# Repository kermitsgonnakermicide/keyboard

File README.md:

# keyboard

a travel sized 60% keyboard with two rotary encoders for extra functionality!<br>

## Design<br>

This keyboard is pretty **bog-standard**, and can be split into two basic components; the PCB and case<br>
**PCB**:<br>
Fully through hole, with a raspberry pi pico, in4018 diodes and HMX macchiato switches(cheap + sound awesome!)<br>
Went fully THT to keep costs as low as I can, and get some real soldering in!<br>
**Case**:<BR>
Just a case covering the entire keyboard t_t
Again, owing to the purpose of the keyboard, I want to keep it small and simple, but for the shiggles I addded this cool pattern to the bottom of my case<br>
<br>

**Firmware**:<br>
Again, pretty standard KMK firmware running on the pico<br>
<br>

## Images

<br>
<br>
<BR>
<br>

### Images of the CAD

## BOM

| ITEM                        | QTY | TOTAL  | SRC                                                                                                                                                                                                                                                                                                                                                                                                                                                                                                                                                                                                                                                                                                                                                                                                                                                                                                                                                                                                                                                                                                                                                                                            | NOTE                                 |
| --------------------------- | --- | ------ | ---------------------------------------------------------------------------------------------------------------------------------------------------------------------------------------------------------------------------------------------------------------------------------------------------------------------------------------------------------------------------------------------------------------------------------------------------------------------------------------------------------------------------------------------------------------------------------------------------------------------------------------------------------------------------------------------------------------------------------------------------------------------------------------------------------------------------------------------------------------------------------------------------------------------------------------------------------------------------------------------------------------------------------------------------------------------------------------------------------------------------------------------------------------------------------------------- | ------------------------------------ |
| HMX Macchiato Linear Switch | 7   | 24.35  | [https://neomacro.in/products/keykobo-rainbow?variant=48680982413590](https://neomacro.in/products/keykobo-rainbow?variant=48680982413590)                                                                                                                                                                                                                                                                                                                                                                                                                                                                                                                                                                                                                                                                                                                                                                                                                                                                                                                                                                                                                                                     | Sold in packs of 10 and I require 62 |
| KeyKobo Rainbow Keycap      | 1   | 43.48  | [https://neomacro.in/products/keykobo-rainbow?variant=48680982413590](https://neomacro.in/products/keykobo-rainbow?variant=48680982413590)                                                                                                                                                                                                                                                                                                                                                                                                                                                                                                                                                                                                                                                                                                                                                                                                                                                                                                                                                                                                                                                     |                                      |
| Raspberry Pi Pico 2         | 1   | 4.79   | [https://www.amazon.in/Raspberry-Pico-All-Microcontroller-Board/dp/B0B69KZBD8/ref=sr_1_1?crid=2SX0N4M63ZWH0&dib=eyJ2IjoiMSJ9.AG5JhGRrljClCgda-pmbDiD1qgK6UMgZNUfO6lCjvNRDwukhXHZauoI63nwYufeCMjrTgOu-PR4EB1B7bBTxMx_hHgDObzbV_989GRUKeAKs9bf6mNNWnI8RB88uI3AtziqfbLDEnSlC9C45SWxsgeOhS_r8351-swVnHh5PpfJFPoSv4LKkKSLkdM34SVLB4KbwTGd2ggQV1Gwpf81-vTKtUTg3C4Jg-lUPle1kBh8.S8F72l44oyaOFh3p5GCZGWSFGbHGolIi6mE-abOFBGI&dib_tag=se&keywords=raspi+pico&qid=1755337610&sprefix=raspi+pic,aps,281&sr=8-1&th=1](https://www.amazon.in/Raspberry-Pico-All-Microcontroller-Board/dp/B0B69KZBD8/ref=sr_1_1?crid=2SX0N4M63ZWH0&dib=eyJ2IjoiMSJ9.AG5JhGRrljClCgda-pmbDiD1qgK6UMgZNUfO6lCjvNRDwukhXHZauoI63nwYufeCMjrTgOu-PR4EB1B7bBTxMx_hHgDObzbV_989GRUKeAKs9bf6mNNWnI8RB88uI3AtziqfbLDEnSlC9C45SWxsgeOhS_r8351-swVnHh5PpfJFPoSv4LKkKSLkdM34SVLB4KbwTGd2ggQV1Gwpf81-vTKtUTg3C4Jg-lUPle1kBh8.S8F72l44oyaOFh3p5GCZGWSFGbHGolIi6mE-abOFBGI&dib_tag=se&keywords=raspi+pico&qid=1755337610&sprefix=raspi+pic,aps,281&sr=8-1&th=1)                                                                                                                                                                             |                                      |
| IN4148 diode                | 100 | 1.74   | [https://www.amazon.in/100PCS-1N4148-IN4148-switching-Switching/dp/B08DYFFYPQ](https://www.amazon.in/100PCS-1N4148-IN4148-switching-Switching/dp/B08DYFFYPQ)                                                                                                                                                                                                                                                                                                                                                                                                                                                                                                                                                                                                                                                                                                                                                                                                                                                                                                                                                                                                                                   |                                      |
| EC11 Encoder                | 2   | 2.06   | [https://www.amazon.in/dp/B0888RVZSN?social_share=cm_sw_r_cp_ud_dp_ECM6496E6Q914JPQP2XQ&\_encoding=UTF8&psc=1](https://www.amazon.in/dp/B0888RVZSN?social_share=cm_sw_r_cp_ud_dp_ECM6496E6Q914JPQP2XQ&_encoding=UTF8&psc=1)                                                                                                                                                                                                                                                                                                                                                                                                                                                                                                                                                                                                                                                                                                                                                                                                                                                                                                                                                                    |                                      |
| PCB Cost                    | 1   | 39.55  | JLCPCB                                                                                                                                                                                                                                                                                                                                                                                                                                                                                                                                                                                                                                                                                                                                                                                                                                                                                                                                                                                                                                                                                                                                                                                         | Without coupon, including shipping   |
| M5 CSK Screws               | 15  | 1.71   | [https://www.amazon.in/RT-SENSE-Countersunk-Machine-tensile/dp/B0CZDXM5NJ/ref=sr_1_4?crid=TGL04IS2H7U4&dib=eyJ2IjoiMSJ9.-ETdl_9o0rQhq2v8QyvieSeZBwawFgI0otkrKzwH_3Kr6CDDPBLv5RKM2_BuHqXBQlgEFxbOraN_T8u7Prs0k_uBT1Lap6PuIfB5L00UkwsWeFqAUkovVYp5cKpsNdlAAAIpJ3XXII_SnrmWUHdrnR_Qm5SZUBb-8-pTL84gnmdmh3BZrIbskamtTstUBqwtsfaHfz_QWUSj6JO8KaddyIW3fzTGaVdQQMOTJFMSkXs3UvAkW26RJIoPtypqXWIEqhShBDmE66IfQqOCSBbTQMD0UUzCtQ2SWeOWagk2JB0.xHmdo73Vnp2HuIfA9RUYqdI207I3gBPz6IcrGBW5zD0&dib_tag=se&keywords=m5+countersunk&qid=1755337697&s=industrial&sprefix=m5+countersu,industrial,263&sr=1-4&th=1](https://www.amazon.in/RT-SENSE-Countersunk-Machine-tensile/dp/B0CZDXM5NJ/ref=sr_1_4?crid=TGL04IS2H7U4&dib=eyJ2IjoiMSJ9.-ETdl_9o0rQhq2v8QyvieSeZBwawFgI0otkrKzwH_3Kr6CDDPBLv5RKM2_BuHqXBQlgEFxbOraN_T8u7Prs0k_uBT1Lap6PuIfB5L00UkwsWeFqAUkovVYp5cKpsNdlAAAIpJ3XXII_SnrmWUHdrnR_Qm5SZUBb-8-pTL84gnmdmh3BZrIbskamtTstUBqwtsfaHfz_QWUSj6JO8KaddyIW3fzTGaVdQQMOTJFMSkXs3UvAkW26RJIoPtypqXWIEqhShBDmE66IfQqOCSBbTQMD0UUzCtQ2SWeOWagk2JB0.xHmdo73Vnp2HuIfA9RUYqdI207I3gBPz6IcrGBW5zD0&dib_tag=se&keywords=m5+countersunk&qid=1755337697&s=industrial&sprefix=m5+countersu,industrial,263&sr=1-4&th=1) |                                      |
|                             |     |        |                                                                                                                                                                                                                                                                                                                                                                                                                                                                                                                                                                                                                                                                                                                                                                                                                                                                                                                                                                                                                                                                                                                                                                                                |                                      |
|                             |     | 117.68 |                                                                                                                                                                                                                                                                                                                                                                                                                                                                                                                                                                                                                                                                                                                                                                                                                                                                                                                                                                                                                                                                                                                                                                                                |                                      |

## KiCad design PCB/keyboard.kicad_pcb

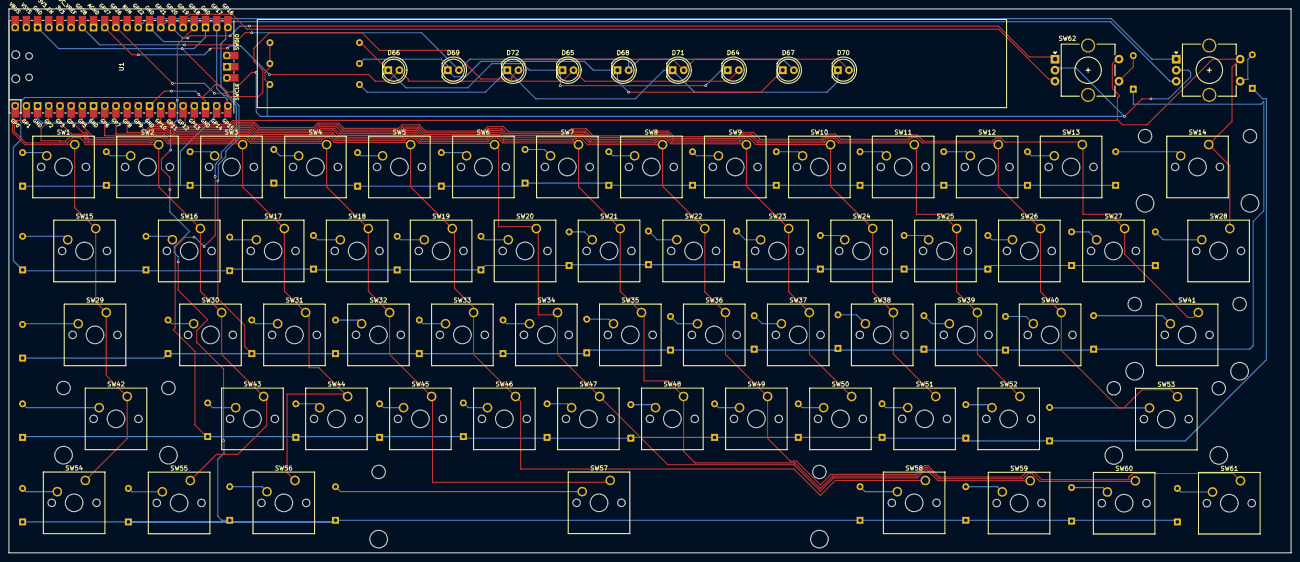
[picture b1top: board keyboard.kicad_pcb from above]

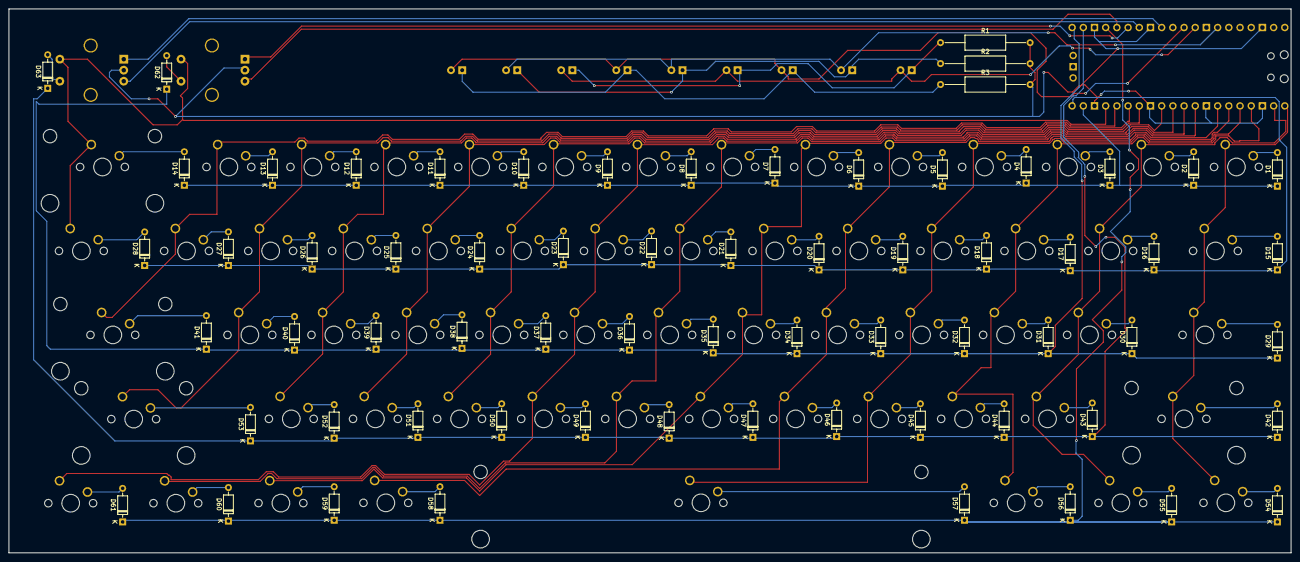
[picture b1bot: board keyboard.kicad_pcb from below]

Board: 2 copper layers, 290.9 x 123.4 mm, 139 parts (66 on the bottom side), 93 nets.

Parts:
D1, D2, D3, D4, D5, D6, D7, D8, D9, D10, D11, D12, D13, D14, D15, D16, D17, D18, D19, D20, D21, D22, D23, D24, D25, D26, D27, D28, D29, D30, D31, D32, D33, D34, D35, D36, D37, D38, D39, D40, D41, D42, D43, D44, D45, D46, D47, D48, D49, D50, D51, D52, D53, D54, D55, D56, D57, D58, D59, D60, D61, D62, D63: 1N4148; D_DO-35_SOD27_P7.62mm_Horizontal
D64, D65, D66, D67, D68, D69, D70, D71, D72: LED_Small; LED_D5.0mm
R1, R2, R3: 330Ω; R_Axial_DIN0309_L9.0mm_D3.2mm_P20.32mm_Horizontal
SW1, SW2, SW3, SW4, SW5, SW6, SW7, SW8, SW9, SW10, SW11, SW12, SW13, SW16, SW17, SW18, SW19, SW20, SW21, SW22, SW23, SW24, SW25, SW26, SW27, SW30, SW31, SW32, SW33, SW34, SW35, SW36, SW37, SW38, SW39, SW40, SW43, SW44, SW45, SW46, SW47, SW48, SW49, SW50, SW51, SW52: SW_Push; SW_Cherry_MX_1.00u_PCB
SW14: SW_Push; SW_Cherry_MX_2.00u_PCB
SW15, SW28: SW_Push; SW_Cherry_MX_1.50u_PCB
SW29: SW_Push; SW_Cherry_MX_1.75u_PCB
SW41, SW42: SW_Push; SW_Cherry_MX_2.25u_PCB
SW53: SW_Push; SW_Cherry_MX_2.75u_PCB
SW54, SW55, SW56, SW58, SW59, SW60, SW61: SW_Push; SW_Cherry_MX_1.25u_PCB
SW57: SW_Push; SW_Cherry_MX_6.25u_PCB
SW62, SW63: RotaryEncoder_Switch; RotaryEncoder_Alps_EC11E-Switch_Vertical_H20mm_CircularMoun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
U1: Pico; RPi_Pico_SMD_TH

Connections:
GND: R1.2, R2.2, R3.2, SW62.C, SW63.C, U1.3 (GND), U1.8 (GND), U1.13 (GND), U1.18 (GND), U1.23 (GND), U1.28 (GND), U1.38 (GND)
unnamed: D1.2 (A), SW1.2
unnamed: D2.2 (A), SW2.2
unnamed: D3.2 (A), SW3.2
unnamed: D4.2 (A), SW4.2
unnamed: D5.2 (A), SW5.2
unnamed: D6.2 (A), SW6.2
unnamed: D7.2 (A), SW7.2
unnamed: D8.2 (A), SW8.2
unnamed: D9.2 (A), SW9.2
unnamed: D10.2 (A), SW10.2
unnamed: D11.2 (A), SW11.2
unnamed: D12.2 (A), SW12.2
unnamed: D13.2 (A), SW13.2
unnamed: D14.2 (A), SW14.2
unnamed: D15.2 (A), SW15.2
unnamed: D16.2 (A), SW16.2
unnamed: D17.2 (A), SW17.2
unnamed: D18.2 (A), SW18.2
unnamed: D19.2 (A), SW19.2
unnamed: D20.2 (A), SW20.2
unnamed: D21.2 (A), SW21.2
unnamed: D22.2 (A), SW22.2
unnamed: D23.2 (A), SW23.2
unnamed: D24.2 (A), SW24.2
unnamed: D25.2 (A), SW25.2
unnamed: D26.2 (A), SW26.2
unnamed: D27.2 (A), SW27.2
unnamed: D28.2 (A), SW28.2
unnamed: D29.2 (A), SW29.2
unnamed: D30.2 (A), SW30.2
unnamed: D31.2 (A), SW31.2
unnamed: D32.2 (A), SW32.2
unnamed: D33.2 (A), SW33.2
unnamed: D34.2 (A), SW34.2
unnamed: D35.2 (A), SW35.2
unnamed: D36.2 (A), SW36.2
unnamed: D37.2 (A), SW37.2
unnamed: D38.2 (A), SW38.2
unnamed: D39.2 (A), SW39.2
unnamed: D40.2 (A), SW40.2
unnamed: D41.2 (A), SW41.2
unnamed: D42.2 (A), SW42.2
unnamed: D43.2 (A), SW43.2
unnamed: D44.2 (A), SW44.2
unnamed: D45.2 (A), SW45.2
unnamed: D46.2 (A), SW46.2
unnamed: D47.2 (A), SW47.2
unnamed: D48.2 (A), SW48.2
unnamed: D49.2 (A), SW49.2
unnamed: D50.2 (A), SW50.2
unnamed: D51.2 (A), SW51.2
unnamed: D52.2 (A), SW52.2
unnamed: D53.2 (A), SW53.2
unnamed: D54.2 (A), SW54.2
unnamed: D55.2 (A), SW55.2
unnamed: D56.2 (A), SW56.2
unnamed: D57.2 (A), SW57.2
unnamed: D58.2 (A), SW58.2
unnamed: D59.2 (A), SW59.2
unnamed: D60.2 (A), SW60.2
unnamed: D61.2 (A), SW61.2
unnamed: D62.2 (A), SW62.S1
unnamed: D63.2 (A), SW63.S1
unnamed: D64.1 (K), D65.1 (K), D66.1 (K), R1.1
unnamed: D67.1 (K), D68.1 (K), D69.1 (K), R2.1
unnamed: D70.1 (K), D71.1 (K), D72.1 (K), R3.1
blue_anode: D67.2 (A), D68.2 (A), D69.2 (A), U1.34 (GPIO28_ADC2)
col1: SW1.1, SW15.1, SW29.1, SW42.1, SW54.1, U1.1 (GPIO0)
col2: SW2.1, SW16.1, SW30.1, SW43.1, SW55.1, U1.2 (GPIO1)
col3: SW3.1, SW17.1, SW31.1, SW44.1, SW56.1, U1.4 (GPIO2)
col4: SW4.1, SW18.1, SW32.1, SW45.1, SW57.1, U1.5 (GPIO3)
col5: SW5.1, SW19.1, SW33.1, SW46.1, SW58.1, U1.6 (GPIO4)
col6: SW6.1, SW20.1, SW34.1, SW47.1, SW59.1, U1.7 (GPIO5)
col7: SW7.1, SW21.1, SW35.1, SW48.1, SW60.1, U1.9 (GPIO6)
col8: SW8.1, SW22.1, SW36.1, SW49.1, SW61.1, U1.10 (GPIO7)
col9: SW9.1, SW23.1, SW37.1, SW50.1, U1.11 (GPIO8)
col10: SW10.1, SW24.1, SW38.1, SW51.1, U1.12 (GPIO9)
col11: SW11.1, SW25.1, SW39.1, SW52.1, U1.14 (GPIO10)
col12: SW12.1, SW26.1, SW40.1, SW53.1, U1.15 (GPIO11)
col13: SW13.1, SW27.1, SW41.1, U1.16 (GPIO12)
col14: SW14.1, SW28.1, SW62.S2, SW63.S2, U1.17 (GPIO13)
green_anode: D70.2 (A), D71.2 (A), D72.2 (A), U1.31 (GPIO26_ADC0)
re1: SW62.B, U1.25 (GPIO19)
re2: SW62.A, U1.26 (GPIO20)
re3: SW63.B, U1.27 (GPIO21)
re4: SW63.A, U1.29 (GPIO22)
red_anode: D64.2 (A), D65.2 (A), D66.2 (A), U1.32 (GPIO27_ADC1)
row1: D1.1 (K), D2.1 (K), D3.1 (K), D4.1 (K), D5.1 (K), D6.1 (K), D7.1 (K), D8.1 (K), D9.1 (K), D10.1 (K), D11.1 (K), D12.1 (K), D13.1 (K), D14.1 (K), U1.19 (GPIO14)
row2: D15.1 (K), D16.1 (K), D17.1 (K), D18.1 (K), D19.1 (K), D20.1 (K), D21.1 (K), D22.1 (K), D23.1 (K), D24.1 (K), D25.1 (K), D26.1 (K), D27.1 (K), D28.1 (K), U1.20 (GPIO15)
row3: D29.1 (K), D30.1 (K), D31.1 (K), D32.1 (K), D33.1 (K), D34.1 (K), D35.1 (K), D36.1 (K), D37.1 (K), D38.1 (K), D39.1 (K), D40.1 (K), D41.1 (K), D62.1 (K), U1.21 (GPIO16)
row4: D42.1 (K), D43.1 (K), D44.1 (K), D45.1 (K), D46.1 (K), D47.1 (K), D48.1 (K), D49.1 (K), D50.1 (K), D51.1 (K), D52.1 (K), D53.1 (K), D63.1 (K), U1.22 (GPIO17)
row5: D54.1 (K), D55.1 (K), D56.1 (K), D57.1 (K), D58.1 (K), D59.1 (K), D60.1 (K), D61.1 (K), U1.24 (GPIO18)

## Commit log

2025-06-13 PCBWOOOO!!!
2025-06-13 oeiaiaiaoio
2025-06-13 editr
2025-06-14 UGHGHG why doesnt my pcb ffile work
2025-06-14 production stuff
2025-06-15 updatez
2025-06-15 FINISHEDEEEEEEEE
2025-06-15 baguette!!
2025-06-21 aaaaaaaaaaaaa!!!
